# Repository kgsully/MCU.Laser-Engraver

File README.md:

# Laser Engraver
## **2 Axis laser engraver using the open source FluidNC Firmware**

This repository contains the PCB schematics and layout design as well as STL models for 3D printed components.

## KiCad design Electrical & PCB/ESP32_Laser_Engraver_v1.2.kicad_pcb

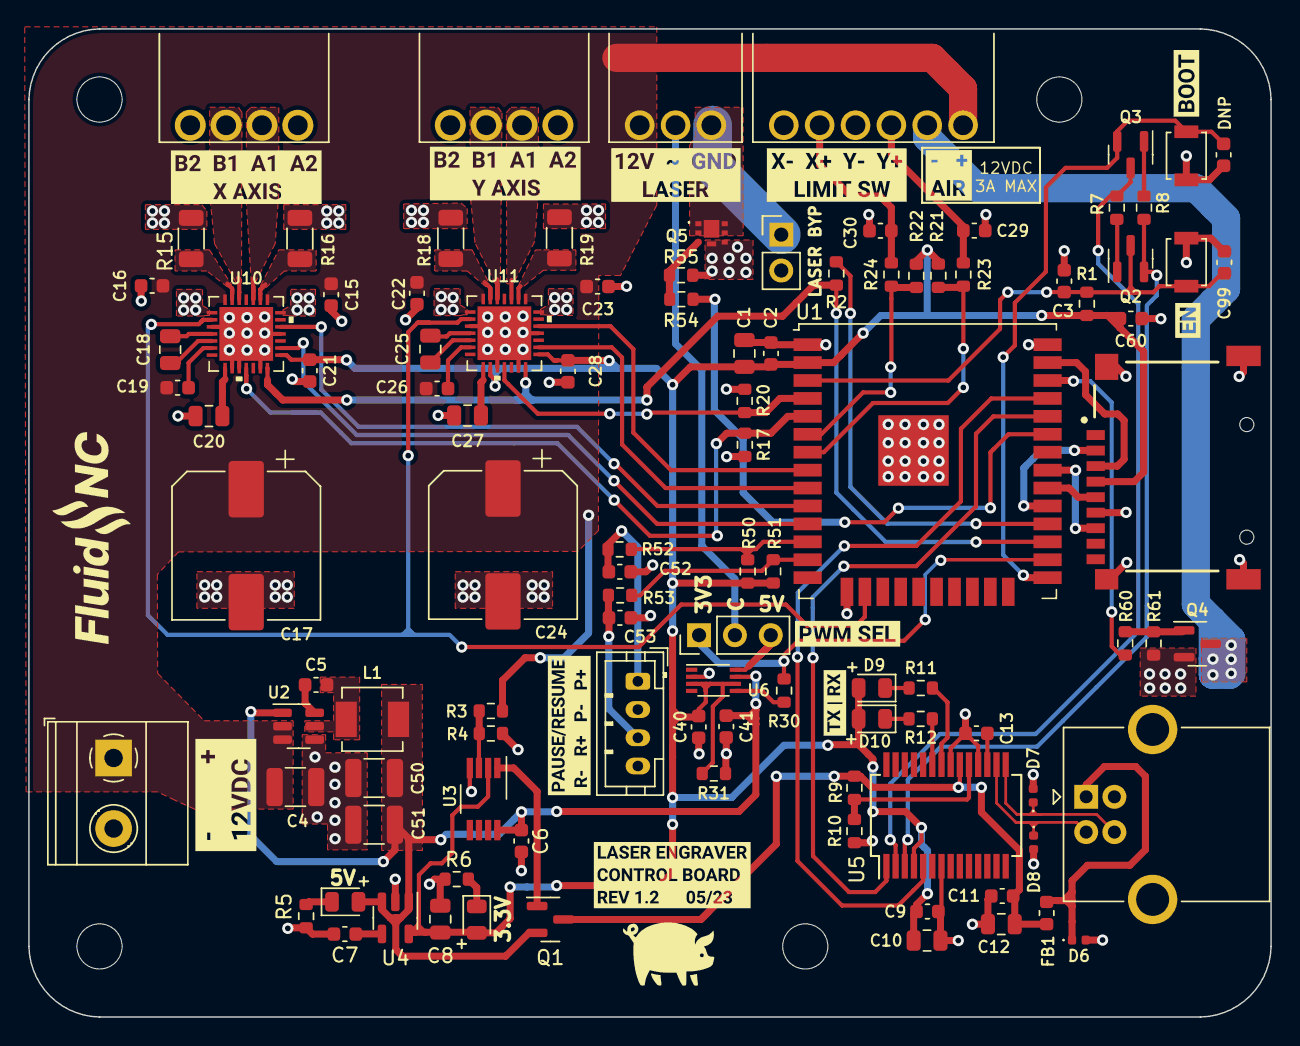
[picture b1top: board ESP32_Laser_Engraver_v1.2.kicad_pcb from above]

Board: 2 copper layers, 88.0 x 70.0 mm, 120 parts (0 on the bottom side), 80 nets.

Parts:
C1: 22u; C_0805_2012Metric
C2, C3, C5, C9, C11, C99: 0.1u; C_0603_1608Metric
C4: 10u; C_1210_3225Metric
C6, C15, C16, C19, C21, C22, C23, C26, C28, C29, C30, C40, C41, C52, C53, C60: 100n; C_0603_1608Metric
C7: 10n; C_0603_1608Metric
C8, C20, C27: 2.2u; C_0805_2012Metric
C10, C12: 4.7u; C_0805_2012Metric
C13: 1u; C_0603_1608Metric
C14: 0u; C_0603_1608Metric
C17, C24: 100u; CP_Elec_10x10
C18, C25: 22n; C_0805_2012Metric
C50, C51: 22u; C_1210_3225Metric
D4: RED; LED_0805_2012Metric
D5, D9, D10: GRN; LED_0805_2012Metric
D6, D7, D8: 5VWM; D_0402_1005Metric
FB1: 40R; L_0603_1608Metric
H1, H2, H3, H4: MountingHole; MountingHole_3.2mm_M3
J2: 1935776; TerminalBlock_Phoenix_MKDS-1,5-2_1x02_P5.00mm_Horizontal
J3: USB_B; USB_B_OST_USB-B1HSxx_Horizontal
J10, J11: Screw_Terminal_01x04; KF2EDGR-2.54-4P
J12: Screw_Terminal_01x06; KF2EDGR-2.54-6P
J20: Screw_Terminal_01x03; KF2EDGR-2.54-3P
J21: Conn_01x02_Male; PinHeader_1x02_P2.54mm_Vertical
J22: Conn_01x03_Male; PinHeader_1x03_P2.54mm_Vertical
J100: TF-01A
J101: Conn_01x04_Male; JST_PH_B4B-PH-K_1x04_P2.00mm_Vertical
L1: 4R7; FXL0420-4R7-M
Q1: DMP2110U-7; SOT-23
Q2, Q3: SS8050-G; SOT-23
Q4: SI2302A-TP; SOT-23
Q5: PMPB23XNEZ
R1, R7, R8, R10, R17, R20, R21, R22, R50, R51, R55, R61: 10k; R_0603_1608Metric
R2, R5, R6, R11, R12, R54, R60: 1k; R_0603_1608Metric
R3: 6.8k; R_0603_1608Metric
R4: 4.7k; R_0603_1608Metric
R9: 4k7; R_0603_1608Metric
R15, R16, R18, R19: 0.14R; R_1206_3216Metric
R23, R24, R52, R53: 100R; R_0603_1608Metric
R30: 0R; R_0603_1608Metric
R31: XXXR; R_0603_1608Metric
SW1, SW2: SW_Push; SW_SPST_B3U-1000P
U1: ESP32-WROOM-32U
U2: AP63205WU; TSOT-23-6
U3: LMV358IDGKR; VSSOP-8_3.0x3.0mm_P0.65mm
U4: SPX3819M5-L-3-3; SOT-23-5
U5: CY7C65213-28PVXI; SSOP-28_5.3x10.2mm_P0.65mm
U6: TXS0102DCU; VSSOP-8_2.3x2mm_P0.5mm
U10, U11: TMC2209
kibuzzard-642C7B83: G***; kibuzzard-642C7B83
kibuzzard-642C73EA: G***; kibuzzard-642C73EA
kibuzzard-642C740F: G***; kibuzzard-642C740F
kibuzzard-642DA7F4: G***; kibuzzard-642DA7F4
kibuzzard-642DA8A0: G***; kibuzzard-642DA8A0
kibuzzard-642DA84C: G***; kibuzzard-642DA84C
kibuzzard-642DA806: G***; kibuzzard-642DA806
kibuzzard-6448BA0F: G***; kibuzzard-6448BA0F
kibuzzard-64653C23: G***; kibuzzard-64653C23
kibuzzard-64653D2F: G***; kibuzzard-64653D2F
kibuzzard-6448424C: G***; kibuzzard-6448424C
kibuzzard-64481964: G***; kibuzzard-64481964

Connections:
+3.3V: C1.1, C2.1, C8.1, C9.2, C10.1, C21.1, C28.1, C40.1, C60.1, D5.2 (A), D9.2 (A), D10.2 (A), J100.4 (VDD), R1.1, R21.2, R22.2, R31.1, R50.2, R51.2, U1.2 (VDD), U3.2 (-), U4.5 (OUT), U5.4 (VCCIO), U6.3 (VCCA), U6.6 (OE), U10.15 (VCC_IO), U11.9 (MS1_AD0), U11.15 (VCC_IO)
+5V: C6.1, C41.1, C50.1, C51.1, D4.2 (A), L1.2, Q1.2 (S), U2.1 (FB), U3.8 (V+), U4.1 (IN), U4.3 (EN), U6.7 (VCCB)
/ESP32 MCU/CS_SD: J100.2 (CD/DAT3), U1.29 (IO5)
/ESP32 MCU/DTR: Q3.3 (C), R7.1, U5.2 (DTR)
/ESP32 MCU/EN: C3.1, C99.2, Q2.3 (C), R1.2, SW2.2, U1.3 (EN)
/ESP32 MCU/IO0: C14.2, Q3.2 (E), SW1.2, U1.25 (IO0)
/ESP32 MCU/IO13: U1.16 (IO13), U10.2 (ENN), U11.2 (ENN)
/ESP32 MCU/IO22: R60.1, U1.36 (IO22)
/ESP32 MCU/IO25: U1.10 (IO25), U10.19 (DIR)
/ESP32 MCU/IO26: U1.11 (IO26), U10.16 (STEP)
/ESP32 MCU/IO32: U1.8 (IO32), U11.19 (DIR)
/ESP32 MCU/IO33: U1.9 (IO33), U11.16 (STEP)
/ESP32 MCU/IO34: R22.1, R24.1, U1.6 (IO34)
/ESP32 MCU/IO35: R21.1, R23.1, U1.7 (IO35)
/ESP32 MCU/IO36: R20.2, U1.4 (SENSOR_VP), U11.11 (DIAG)
/ESP32 MCU/IO39: R17.2, U1.5 (SENSOR_VN), U10.11 (DIAG)
/ESP32 MCU/LASER_EN: R54.1, U1.33 (IO21)
/ESP32 MCU/LASER_RET: J20.1, J21.1, Q5.1 (D_1), Q5.2 (D_2), Q5.5 (D_3), Q5.6 (D_4), Q5.7 (D_5)
/ESP32 MCU/MISO: J100.7 (DAT0), U1.31 (IO19)
/ESP32 MCU/MOSI: J100.3 (CMD), U1.37 (IO23)
/ESP32 MCU/PAUSE: R50.1, R52.1, U1.12 (IO27)
/ESP32 MCU/PWM_3V3: J22.1, R30.1, U1.26 (IO4)
/ESP32 MCU/PWM_5V: J22.3, U6.8 (B1)
/ESP32 MCU/RESUME: R51.1, R53.1, U1.13 (IO14)
/ESP32 MCU/RTS: Q2.2 (E), R8.2, U5.3 (RTS)
/ESP32 MCU/RXD: U1.35 (TXD0/IO1), U5.5 (RXD)
/ESP32 MCU/SCK: J100.5 (CLK), U1.30 (IO18)
/ESP32 MCU/TMC_UART: R2.2, U1.27 (IO16), U10.14 (PDN_UART), U11.14 (PDN_UART)
/ESP32 MCU/TXD: U1.34 (RXD0/IO3), U5.1 (TXD)
/Power Supply/5V_SW: C5.2, L1.1, U2.5 (SW)
/Power Supply/VBUS: C11.2, C12.1, FB1.2, Q1.3 (D), R9.2, U5.20 (VCC)
/Stepper Motor Circuits/AIR: J12.2, Q4.3 (D)
/Stepper Motor Circuits/X_BRA: R16.1, U10.23 (BRA)
/Stepper Motor Circuits/X_BRB: R15.1, U10.27 (BRB)
/Stepper Motor Circuits/X_OA1: J10.2, U10.24 (OA1)
/Stepper Motor Circuits/X_OA2: J10.1, U10.21 (OA2)
/Stepper Motor Circuits/X_OB1: J10.3, U10.26 (OB1)
/Stepper Motor Circuits/X_OB2: J10.4, U10.1 (OB2)
/Stepper Motor Circuits/Y_BRA: R19.1, U11.23 (BRA)
/Stepper Motor Circuits/Y_BRB: R18.1, U11.27 (BRB)
/Stepper Motor Circuits/Y_OA1: J11.2, U11.24 (OA1)
/Stepper Motor Circuits/Y_OA2: J11.1, U11.21 (OA2)
/Stepper Motor Circuits/Y_OB1: J11.3, U11.26 (OB1)
/Stepper Motor Circuits/Y_OB2: J11.4, U11.1 (OB2)
/USB-UART Interface/USB_D+: D7.1 (A1), J3.3 (D+), U5.15 (USBDP)
/USB-UART Interface/USB_D-: D8.1 (A1), J3.2 (D-), U5.16 (USBDM)
GND: C1.2, C2.2, C3.2, C4.2, C6.2, C7.2, C8.2, C9.1, C10.2, C11.1, C12.2, C13.2, C14.1, C15.2, C16.2, C17.2, C20.1, C21.2, C22.2, C23.2, C24.2, C27.1, C28.2, C29.2, C30.2, C40.2, C41.2, C50.2, C51.2, C52.2, C53.2, C60.2, C99.1, D6.2 (A2), D7.2 (A2), D8.2 (A2), J2.2, J3.4 (GND), J12.4, J12.6, J21.2, J100.6 (VSS), J100.MP1 (GND), J100.MP2 (GND), J100.MP3 (GND), J100.MP4 (GND), J101.2, J101.4, Q4.2 (S), Q5.4 (S_1), Q5.8 (S_2), R4.2, R5.2, R6.2, R10.1, R15.2, R16.2, R17.1, R18.2, R19.2, R20.1, R31.2, R55.2, R61.2, SW1.1, SW2.1, U1.1 (GND), U1.15 (GND), U1.38 (GND), U1.39 (GND), U2.4 (GND), U3.4 (V-), U4.2 (GND), U5.7 (GND), U5.18 (GND), U5.21 (GND), U6.2 (GND), U10.3 (GND), U10.9 (MS1_AD0), U10.10 (MS2_AD1), U10.13 (CLK), U10.18 (GND), U10.29 (GND), U11.3 (GND), U11.10 (MS2_AD1), U11.13 (CLK), U11.18 (GND), U11.29 (GND)
unnamed: C5.1, U2.6 (BST)
unnamed: C7.1, U4.4 (BP)
unnamed: C13.1, U5.17 (VCCD)
unnamed: C18.1, U10.4 (CPO)
unnamed: C18.2, U10.5 (CPI)
unnamed: C19.2, U10.6 (VCP)
unnamed: C20.2, U10.8 (5VOUT)
unnamed: C25.1, U11.4 (CPO)
unnamed: C25.2, U11.5 (CPI)
unnamed: C26.2, U11.6 (VCP)
unnamed: C27.2, U11.8 (5VOUT)
unnamed: C29.1, J12.3, R23.2
unnamed: C30.1, J12.5, R24.2
unnamed: C52.1, J101.1, R52.2
unnamed: C53.1, J101.3, R53.2
unnamed: D4.1 (K), R5.1
unnamed: D5.1 (K), R6.1
unnamed: D6.1 (A1), FB1.1, J3.1 (VBUS)
unnamed: D9.1 (K), R11.2
unnamed: D10.1 (K), R12.2
unnamed: J20.2, J22.2
unnamed: Q1.1 (G), U3.1
unnamed: Q2.1 (B), R7.2
unnamed: Q3.1 (B), R8.1
unnamed: Q4.1 (G), R60.2, R61.1
unnamed: Q5.3 (G), R54.2, R55.1
unnamed: R2.1, U1.28 (IO17)
unnamed: R3.2, R4.1, U3.3 (+)
unnamed: R9.1, R10.2, U5.19 (~RESET)
unnamed: R11.1, U5.22 (GPIO1)
unnamed: R12.1, U5.23 (GPIO0)
unnamed: R30.2, U6.5 (A1)
VMOT: C4.1, C15.1, C16.1, C17.1, C19.1, C22.1, C23.1, C24.1, C26.1, J2.1, J12.1, J20.3, R3.1, U2.2 (EN), U2.3 (IN), U10.22 (VS), U10.28 (VS), U11.22 (VS), U11.28 (VS)

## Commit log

2023-05-03 Initial Commit - VERY WIP
    Initial commit for laser engraver PCB and frame parts design. Very WIP still
2023-05-05 Mechanical Model Update
2023-05-05 Updated laser carriage models
2023-05-07 Inside support CAD model update
2023-05-17 Electrical schematic & PCB layout udpate
    Updated to allow selection / bypass of 3.3V - 5V level converter on laser PWM signal. Laser enable now 3V3 from MCU instead of level converting. This should prevent laser from actuating at power up d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
2023-05-18 Added configuration files
    Added FluidNC configuration and USB-UART Bridge configuration files
2025-01-30 Update README.md
    Updated description and added links to pictures
